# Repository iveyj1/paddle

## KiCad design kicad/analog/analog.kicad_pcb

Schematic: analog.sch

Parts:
C101, C102: 10uF; SMD_1206
C103, C104: 100uF; CP_Radial_D6.3mm_P2.50mm
D101: SS24FL; D_SOD-123
J101: FCI 20021221-00014T4LF; conn_FCI_14_NH
R101: 100k; SMD_0805
U101: NCP694-3.3; SOT89-5

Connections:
+3.3VA: C102.1, C104.1, D101.2, U101.5; also elsewhere on the board
/+3.3V_AN_ENABLE: J101.14, R101.2, U101.3
/+V_UNREG_SW: C101.1, C103.1, D101.1, J101.12, U101.4
/AN0_CS*: J101.5; also elsewhere on the board
/AN1_CS*: J101.3; also elsewhere on the board
/AN2_CS*: J101.1; also elsewhere on the board
/AN3_CS*: J101.2; also elsewhere on the board
/I2C_SCK: J101.6
/I2C_SDA: J101.8
/PIO_A: J101.10
/PIO_B_BUSY*: J101.4; also elsewhere on the board
/SPI_MISO: J101.9; also elsewhere on the board
/SPI_MOSI: J101.7; also elsewhere on the board
/SPI_SCLK: J101.11; also elsewhere on the board
GND: C101.2, C102.2, C103.2, C104.2, J101.13, R101.1, U101.2; also elsewhere on the board

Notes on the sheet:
Note: connector pinout is mirror-image to processor board

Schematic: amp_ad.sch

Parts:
C201, C202, C203: 100pF; SMD_0805
C204, C206, C207: 0.1uF; SMD_0805
C205: 10uF; SMD_1206
Q201: DMG3414U; SOT-23
R201, R205: 10.0k; SMD_0805
R202: 20.0k; SMD_0805
R203, R204: DNP; SMD_0805
U201: LTC2052; TSSOP-8_3x3mm_Pitch0.65mm
U202: ADS1220; TSSOP-16-1EP_4.4x5mm_Pitch0.65mm

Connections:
+3.3VA: C204.2, C205.1, C206.2, C207.2, R205.1, U201.8 (V+), U202.12, U202.13; also elsewhere on the board
/AN0_CS*: U202.2; also elsewhere on the board
/BRIDGE_COMP: R202.2; also elsewhere on the board
/IN_0: R201.2; also elsewhere on the board
/PIO_B_BUSY*: Q201.3; also elsewhere on the board
/SPI_MISO: U202.15; also elsewhere on the board
/SPI_MOSI: U202.16; also elsewhere on the board
/SPI_SCLK: U202.1; also elsewhere on the board
/VREF: U202.11; also elsewhere on the board
GND: C201.1, C202.1, C203.2, C204.1, C205.2, C206.1, C207.1, Q201.2, U201.4 (V-), U202.3, U202.4, U202.5, U202.6, U202.8; also elsewhere on the board
unnamed: C201.2, R201.1, R203.1, U201.3 (+)
unnamed: C202.2, R202.1, R204.1, U201.5 (+)
unnamed: C203.1, R205.2, U202.9
unnamed: Q201.1, U202.14
unnamed: R203.2, U201.1, U201.2 (-), U202.10
unnamed: R204.2, U201.6 (-), U201.7, U202.7

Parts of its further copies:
C501, C502, C503, C601, C602, C603, C701, C702, C703: 100pF; SMD_0805
C504, C506, C507, C604, C606, C607, C704, C706, C707: 0.1uF; SMD_0805
C505, C605, C705: 10uF; SMD_1206
Q501, Q601, Q701: DMG3414U; SOT-23
R501, R505, R601, R605, R701, R705: 10.0k; SMD_0805
R502, R602, R702: 20.0k; SMD_0805
R503, R504, R603, R604, R703, R704: DNP; SMD_0805
U501, U601, U701: LTC2052; TSSOP-8_3x3mm_Pitch0.65mm
U502, U602, U702: ADS1220; TSSOP-16-1EP_4.4x5mm_Pitch0.65mm

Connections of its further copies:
+3.3VA: C504.2, C505.1, C506.2, C507.2, C604.2, C605.1, C606.2, C607.2, C704.2, C705.1, C706.2, C707.2, R505.1, R605.1, R705.1, U501.8 (V+), U502.12, U502.13, U601.8 (V+), U602.12, U602.13, U701.8 (V+), U702.12, U702.13; also elsewhere on the board
/AN1_CS*: U502.2; also elsewhere on the board
/AN2_CS*: U602.2; also elsewhere on the board
/AN3_CS*: U702.2; also elsewhere on the board
/BRIDGE_COMP: R502.2, R602.2, R702.2; also elsewhere on the board
/IN_1: R501.2; also elsewhere on the board
/IN_2: R601.2; also elsewhere on the board
/IN_3: R701.2; also elsewhere on the board
/PIO_B_BUSY*: Q501.3, Q601.3, Q701.3; also elsewhere on the board
/SPI_MISO: U502.15, U602.15, U702.15; also elsewhere on the board
/SPI_MOSI: U502.16, U602.16, U702.16; also elsewhere on the board
/SPI_SCLK: U502.1, U602.1, U702.1; also elsewhere on the board
/VREF: U502.11, U602.11, U702.11; also elsewhere on the board
GND: C501.1, C502.1, C503.2, C504.1, C505.2, C506.1, C507.1, C601.1, C602.1, C603.2, C604.1, C605.2, C606.1, C607.1, C701.1, C702.1, C703.2, C704.1, C705.2, C706.1, C707.1, Q501.2, Q601.2, Q701.2, U501.4 (V-), U502.3, U502.4, U502.5, U502.6, U502.8, U601.4 (V-), U602.3, U602.4, U602.5, U602.6, U602.8, U701.4 (V-), U702.3, U702.4, U702.5, U702.6, U702.8; also elsewhere on the board
unnamed: C501.2, R501.1, R503.1, U501.3 (+)
unnamed: C502.2, R502.1, R504.1, U501.5 (+)
unnamed: C503.1, R505.2, U502.9
unnamed: C601.2, R601.1, R603.1, U601.3 (+)
unnamed: C602.2, R602.1, R604.1, U601.5 (+)
unnamed: C603.1, R605.2, U602.9
unnamed: C701.2, R701.1, R703.1, U701.3 (+)
unnamed: C702.2, R702.1, R704.1, U701.5 (+)
unnamed: C703.1, R705.2, U702.9
unnamed: Q501.1, U502.14
unnamed: Q601.1, U602.14
unnamed: Q701.1, U702.14
unnamed: R503.2, U501.1, U501.2 (-), U502.10
unnamed: R504.2, U501.6 (-), U501.7, U502.7
unnamed: R603.2, U601.1, U601.2 (-), U602.10
unnamed: R604.2, U601.6 (-), U601.7, U602.7
unnamed: R703.2, U701.1, U701.2 (-), U702.10
unnamed: R704.2, U701.6 (-), U701.7, U702.7

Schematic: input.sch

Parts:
J301: CONN_02X05; header-0.050-10-pin-through-hole
R301, R302, R303, R304: 10.0k 0.1%; R_0805
U301: SP3003-04; SMD_SC70-6

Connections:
+3.3VA: J301.1, U301.5; also elsewhere on the board
/IN_0: R301.2, U301.4; also elsewhere on the board
/IN_1: R302.2, U301.6; also elsewhere on the board
/IN_2: R303.2, U301.1; also elsewhere on the board
/IN_3: R304.2, U301.3; also elsewhere on the board
GND: J301.10, U301.2; also elsewhere on the board
unnamed: J301.2, R301.1
unnamed: J301.4, R302.1
unnamed: J301.6, R303.1
unnamed: J301.8, R304.1

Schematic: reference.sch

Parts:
C401, C405: 10uF; SMD_1206
C404, C406: 1uF; SMD_0805
R401: 20k 0.1%; SMD_0805
R402: 20.0k 0.1%; SMD_0805
R404: 1R0; SMD_0805
U401: REF5030; TSSOP-8_3x3mm_Pitch0.65mm

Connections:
+3.3VA: C401.2, R401.2, U401.2; also elsewhere on the board
/BRIDGE_COMP: R401.1, R402.2; also elsewhere on the board
/VREF: C406.1, R404.2, U401.6; also elsewhere on the board
GND: C401.1, C404.2, C405.2, C406.2, R402.1, U401.4; also elsewhere on the board
unnamed: C404.1, U401.5
unnamed: C405.1, R404.1

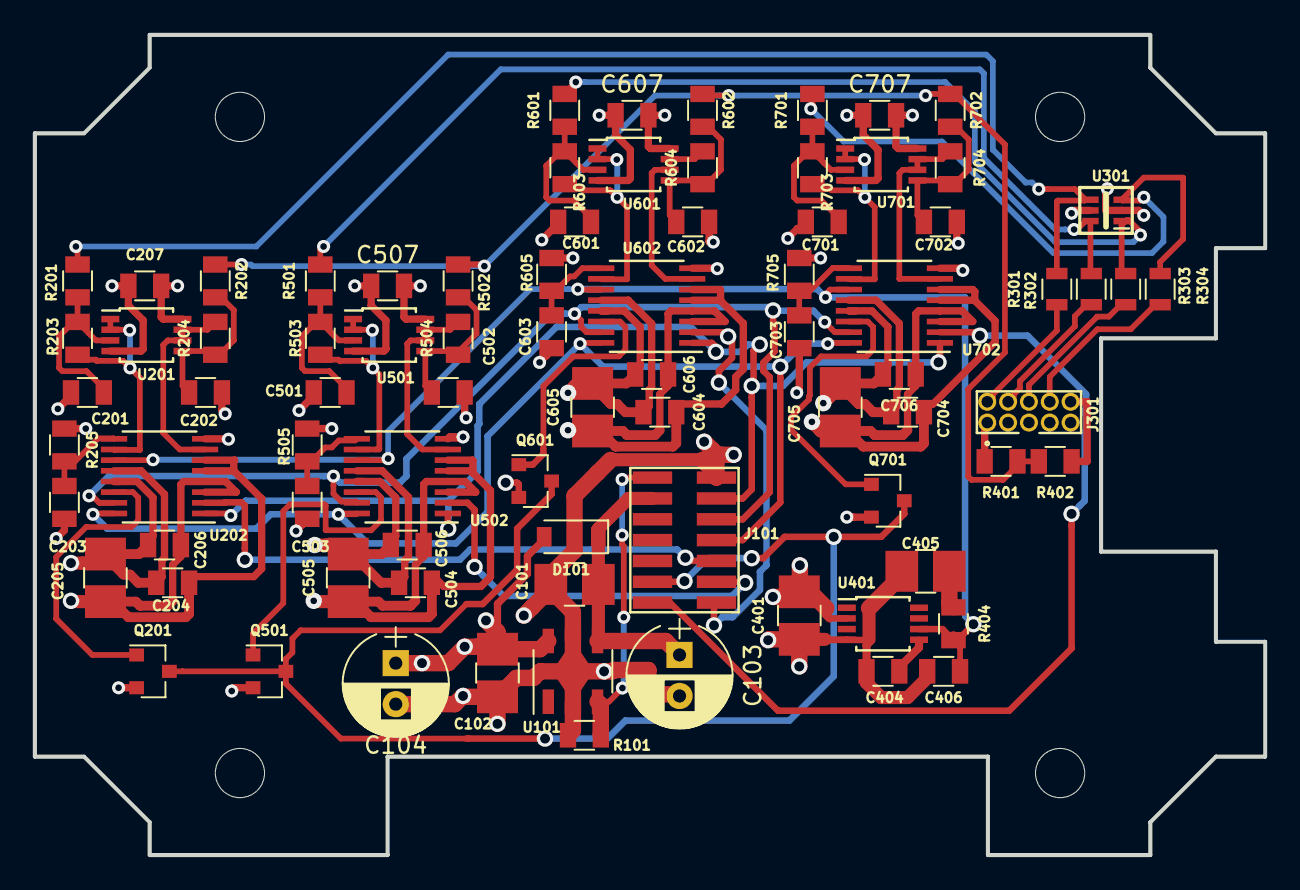
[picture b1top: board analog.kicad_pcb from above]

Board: 4 copper layers, 75.0 x 50.0 mm, 82 parts (0 on the bottom side), 48 nets.

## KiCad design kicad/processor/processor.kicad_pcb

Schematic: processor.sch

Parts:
C101: 1uF; SMD_0805
C102: 10uF; SMD_0805
C103, C104: 0.1uF; SMD_0805
J101: CONN_02X07; conn_FCI_14_NH
LED101, LED102, LED103, LED104, LED105, LED106: LED; SMD_D_0805
R101, R104: 10k; R_0603
R102, R103: 4.7k; R_0603
R105, R106, R108, R109: 330; R_0603
R107, R110: 220; R_0603
U101: ESP32-WROOM
U102: BME280
U103: TCA9534A; SOIC-16

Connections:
+3V3: C102.1, C103.1, C104.1, R101.1, R102.1, R103.1, R104.1, R105.1, U101.2, U102.2, U102.6, U102.8, U103.16; also elsewhere on the board
/1PPS: U101.4; also elsewhere on the board
/+3.3VA_ENABLE: J101.13, U103.9
/+V_UNREG_SW: J101.11; also elsewhere on the board
/AN0_CS*: J101.6, U101.11
/AN1_CS*: J101.4, U101.10
/AN2_CS*: J101.2, U101.9
/AN3_CS*: J101.1, U101.8
/BLINK: R106.1, U101.16
/BOOTLOAD*: U101.25; also elsewhere on the board
/CON_RXD: U101.34; also elsewhere on the board
/CON_TXD: LED101.1, U101.35; also elsewhere on the board
/GPS_ENABLE*: U103.10; also elsewhere on the board
/GPS_RXD: U101.27; also elsewhere on the board
/GPS_TXD: U101.28; also elsewhere on the board
/I2C_SCK: J101.5, R102.2, U101.36, U102.4, U103.14
/I2C_SDA: J101.7, R103.2, U101.33, U102.3, U103.15
/KEEPALIVE: U101.26; also elsewhere on the board
/LEDB: R110.1, U103.7
/LEDG: R107.1, U103.6
/LEDR: R108.1, U103.4
/LEDY: R109.1, U103.5
/PIO_A: J101.9, U103.12
/PIO_B_BUSY*: J101.3, R104.2, U101.7
/POWER_SW*: U101.6; also elsewhere on the board
/RESET_ESP*: C101.1, R101.2, U101.3; also elsewhere on the board
/SD_CS*: U101.29; also elsewhere on the board
/SD_ENABLE*: U103.11; also elsewhere on the board
/SD_MISO: U101.31; also elsewhere on the board
/SD_MOSI: U101.37; also elsewhere on the board
/SD_SCLK: U101.30; also elsewhere on the board
/SPI_MISO: J101.10, U101.13
/SPI_MOSI: J101.8, U101.12
/SPI_SCLK: J101.12, U101.14
GND: C101.2, C102.2, C103.2, C104.2, J101.14, LED102.1, LED103.1, LED104.1, LED105.1, LED106.1, U101.1, U101.15, U101.38, U101.39, U102.1, U102.5, U102.7, U103.1, U103.2, U103.3, U103.8; also elsewhere on the board
unnamed: LED101.2, R105.2
unnamed: LED102.2, R106.2
unnamed: LED103.2, R107.2
unnamed: LED104.2, R108.2
unnamed: LED105.2, R109.2
unnamed: LED106.2, R110.2

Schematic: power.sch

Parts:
C201, C203: 4.7uF; SMD_0805
C202: 10uF; SMD_0805
C204, C205: 100uF/10V; CP_Radial_D6.3mm_P2.50mm
D201, D202, D203, D204: SS24FL; D_SOD-123
F201: 1A Poly; SMD_1812
J201, J203: S2B-PH-K-S(LF)(SN); JST_battery_header_B2B-PH-K-S
LED201: LED; SMD_D_0805
Q201, Q202, Q204, Q205: DMG3415U; SOT-23
Q203: DMG3414U; SOT-23
R201, R202, R210: 1.0Meg; R_0603
R203: 1.0K; R_0603
R204, R205: 100k; R_0603
R206: 1.0k; R_0603
R207, R208: 1Meg; R_0603
R209: 10K; R_0603
R211: 1R0; R_0603
SW201: SW; SW_KMR7
U201: MCP73832; SOT-23-5
U202: NCP694-3.3; SOT89-5

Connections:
+3V3: C205.1, D204.2, U202.5; also elsewhere on the board
/+V_UNREG_SW: C204.1, D204.1, Q204.3, U202.3, U202.4; also elsewhere on the board
/KEEPALIVE: D203.2; also elsewhere on the board
/POWER_SW*: R204.1; also elsewhere on the board
/USB/+VBUS: Q201.1, Q202.3, R202.1; also elsewhere on the board
/power/V+BAT: F201.2, J203.1
/power/V+BAT_FUSED: C203.1, F201.1, Q205.3, U201.3 (Vbat)
/power/V+EXT: C201.1, D201.2, Q201.2, Q202.2, Q205.1, R203.1, R210.2, U201.4 (VDD)
/power/V_UNREG: Q204.2, R208.2, R211.1, SW201.2
GND: C201.2, C202.2, C203.2, C204.2, C205.2, J201.2, J203.2, Q203.2, R201.2, R202.2, R205.1, R207.1, R209.1, R210.1, U201.2 (Vss), U202.2; also elsewhere on the board
unnamed: C202.1, D203.1, Q203.1, R206.1, R207.2
unnamed: D201.1, Q205.2, R211.2
unnamed: D202.1, R206.2
unnamed: D202.2, R204.2, R205.2, SW201.1
unnamed: J201.1, Q201.3, Q202.1, R201.1
unnamed: LED201.1, U201.1 (STAT)
unnamed: LED201.2, R203.2
unnamed: Q203.3, Q204.1, R208.1
unnamed: R209.2, U201.5 (PROG)

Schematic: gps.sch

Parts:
BT301: CR1025; CR1025_holder
C301: 10uF; SMD_0805
C302: 0.01uF; SMD_0805
C303: 1uF; SMD_0805
L301: bead; SMD_0805
LED301: LED; SMD_D_0805
Q301: DMG3415U; SOT-23
R301: 1MEG; R_0603
R302, R303, R304: 330; R_0603
U301: FGPMMOPA6H

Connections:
+3V3: Q301.2, R301.1; also elsewhere on the board
/1PPS: U301.13; also elsewhere on the board
/GPS_ENABLE*: Q301.1, R301.2; also elsewhere on the board
/GPS_RXD: R302.1; also elsewhere on the board
/GPS_TXD: R303.1; also elsewhere on the board
GND: BT301.-, C301.2, C302.2, C303.2, LED301.1, U301.3, U301.8, U301.12, U301.19; also elsewhere on the board
unnamed: BT301.+, C303.1, U301.4
unnamed: C301.1, C302.1, L301.1, U301.1
unnamed: L301.2, Q301.3
unnamed: LED301.2, R304.1
unnamed: R302.2, U301.9
unnamed: R303.2, U301.10
unnamed: R304.2, U301.5

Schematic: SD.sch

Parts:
C501: 10uF; SMD_1206
C502: 0.1uF; SMD_0805
M501: MICROSD
Q501: DMG3415U; SOT-23
R501: 1MEG; SMD_0805

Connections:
+3V3: R501.2; also elsewhere on the board
/BOOTLOAD*: Q501.3; also elsewhere on the board
GND: C501.2, C502.2; also elsewhere on the board
unnamed 44: C501.1, C502.1; also elsewhere on the board
unnamed 66: Q501.1; also elsewhere on the board
unnamed 67: Q501.2; also elsewhere on the board
unnamed 74: R501.1; also elsewhere on the board

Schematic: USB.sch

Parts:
C501: 10uF; SMD_0805
C502: 0.1uF; SMD_0805
LED501, LED502: LED; SMD_D_0805
Q501, Q502: MMBT4401; SOT-23
R501: 1k; R_0603
R502, R503: 330; R_0603
R504, R505: 10k; R_0603
SW501, SW502: SWITCH_PUSHBUTTON; SW_KMR7
TP501: RXD; tp_th_1mm
TP502: TXD; tp_th_1mm
U501: USB_B_Socket; USB_micro_B_FCI_10104110
U502: SP3003-04; SMD_SC70-6
U503: CP2102N; QFP_24

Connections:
+3V3: R501.2; also elsewhere on the board
/BOOTLOAD*: Q501.3, SW502.1; also elsewhere on the board
/CON_RXD: TP502.1, U503.21; also elsewhere on the board
/CON_TXD: TP501.1, U503.20; also elsewhere on the board
/RESET_ESP*: Q502.3, SW501.1; also elsewhere on the board
/USB/+VBUS: U501.1, U502.1, U503.7, U503.8; also elsewhere on the board
GND: C501.2, C502.2, SW501.2, SW502.2, U501.5, U501.6, U502.2, U503.2, U503.25; also elsewhere on the board
unnamed: C501.1, C502.1, LED501.2, LED502.2, U503.6
unnamed: LED501.1, R502.2
unnamed: LED502.1, R503.2
unnamed: Q501.1, R505.2
unnamed: Q501.2, R504.2, U503.23
unnamed: Q502.1, R504.1
unnamed: Q502.2, R505.1, U503.19
unnamed: R501.1, U503.9
unnamed: R502.1, U503.14
unnamed: R503.1, U503.13
unnamed 77: U503.5; also elsewhere on the board
unnamed: U501.2, U502.3, U503.4
unnamed: U501.3, U502.4, U503.3

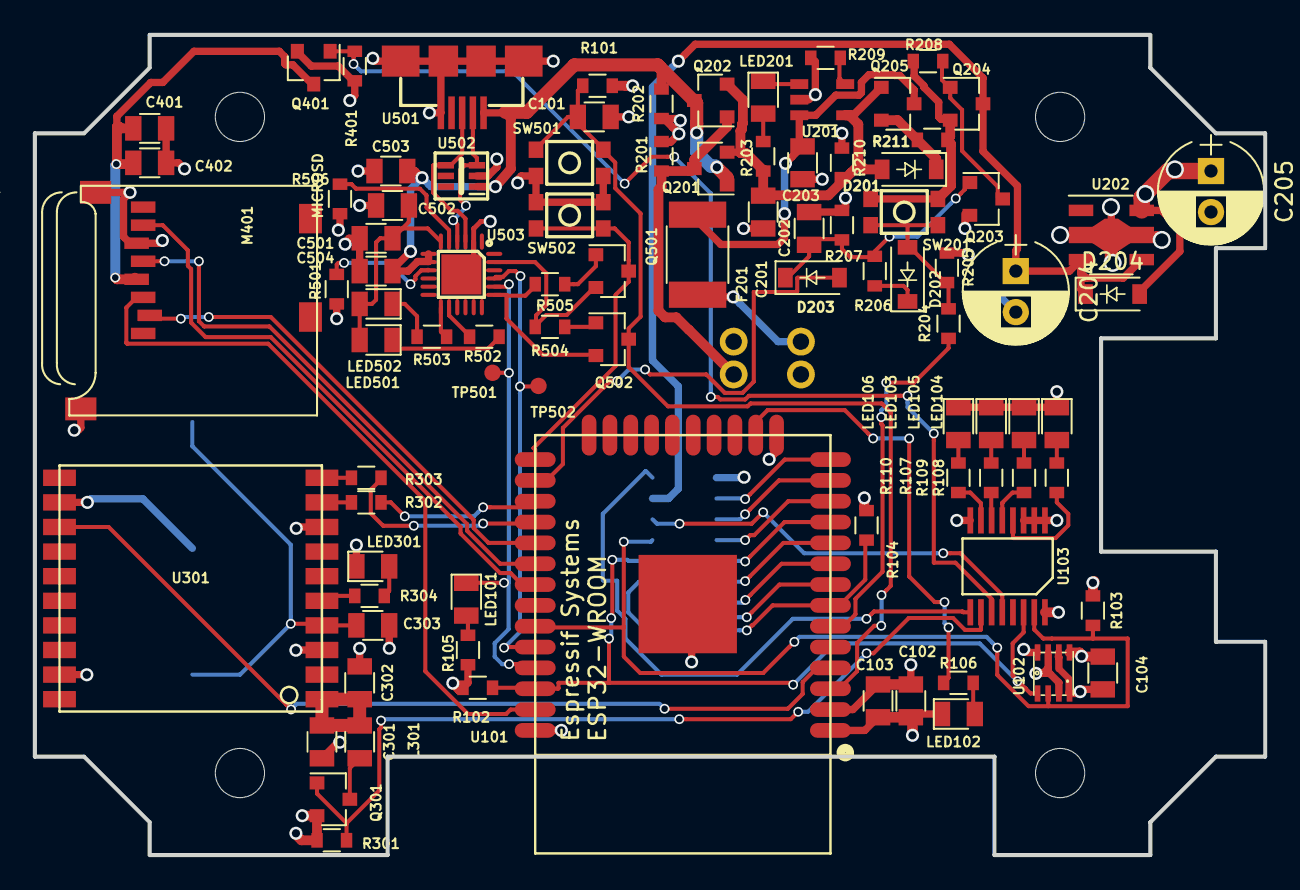
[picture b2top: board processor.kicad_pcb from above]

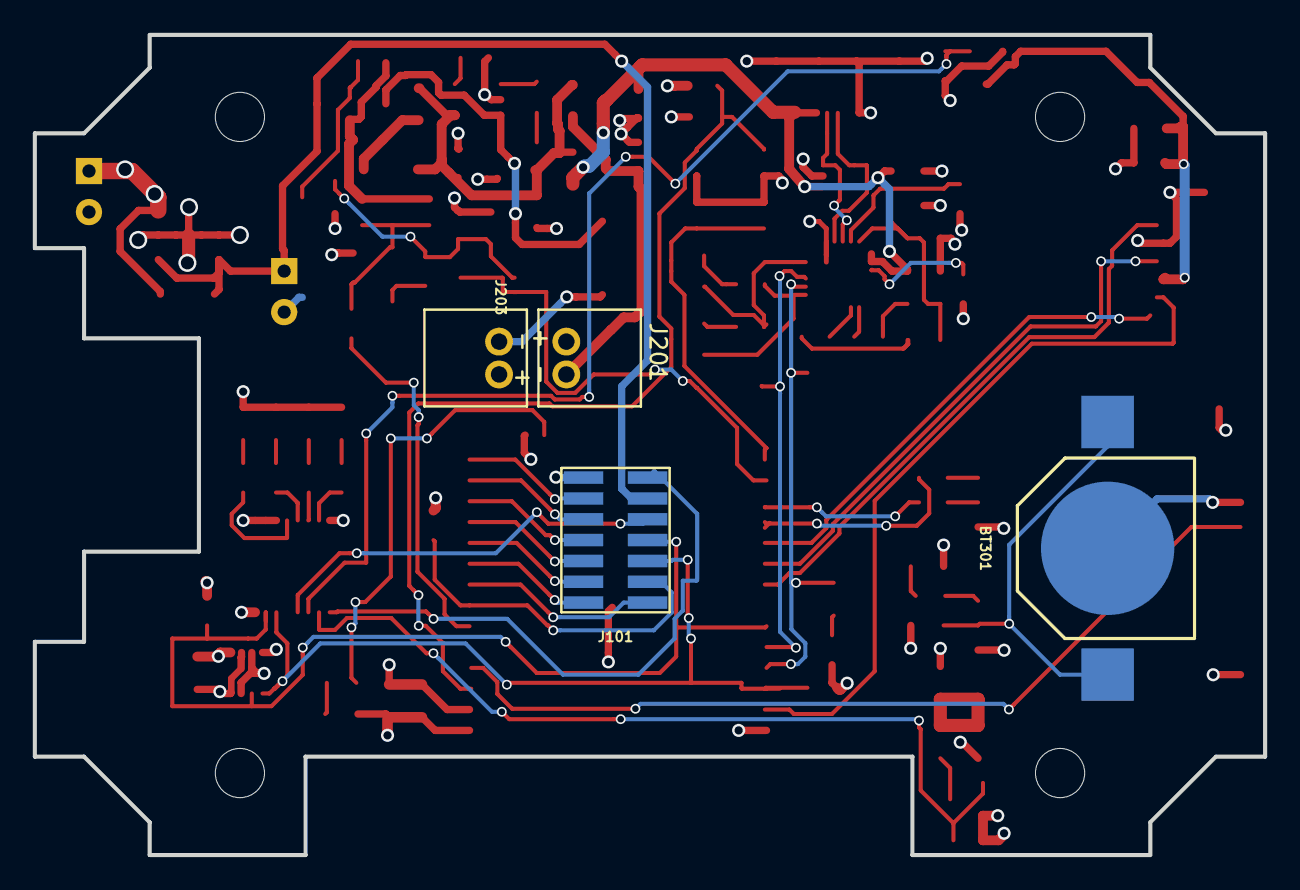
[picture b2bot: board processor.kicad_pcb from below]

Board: 4 copper layers, 75.0 x 50.0 mm, 94 parts (4 on the bottom side), 76 nets.

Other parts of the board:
C401: 10uF; SMD_0805
C402, C504: 0.1uF; SMD_0805
C503: 4.7uF; SMD_0805
M401: MICROSD
Q401: DMG3415U; SOT-23
R401: 1MEG; R_0603
R506: 1k; R_0603

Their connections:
+3V3: Q401.2, R401.1, R506.1; also elsewhere on the board
/SD_CS*: M401.2; also elsewhere on the board
/SD_ENABLE*: Q401.1, R401.2; also elsewhere on the board
/SD_MISO: M401.7; also elsewhere on the board
/SD_MOSI: M401.3; also elsewhere on the board
/SD_SCLK: M401.5; also elsewhere on the board
/USB/+VBUS: C503.1, C504.1; also elsewhere on the board
GND: C401.2, C402.2, C503.2, C504.2, M401.6, M401.MT1, M401.MT2; also elsewhere on the board
unnamed: C401.1, C402.1, M401.4, Q401.3
unnamed 77: R506.2; also elsewhere on the board

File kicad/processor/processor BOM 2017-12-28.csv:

Id,Designator,Package,Quantity,Designation,Supplier and ref
8,U101,ESP32-WROOM,1,ESP32-WROOM,1 stock
25,U301,FGPMMOPA6H,1,FGPMMOPA6H,1 stock
18,F201,SMD_1812,1,1A Poly,10 stock
24,SW201,SW_KMR7,1,SW,10 stock
12,"SW501,SW502",SW_KMR7,2,SWITCH_PUSHBUTTON,10 stock
29,"C303,C101",SMD_0805,2,1uF,100 stock
3,"C401,C301,C202,C102,C205,C204,C501",SMD_0805,7,10uF,100 stock
23,U202,SOT89-5,1,NCP694-3.3,17 stock
41,Q203,SOT-23,1,DMG3414U,20 stock
11,"Q301,Q401,Q205,Q204,Q202,Q201",SOT-23,6,DMG3415U,20 stock
28,"C402,C104,C103,C502",SMD_0805,4,0.1uF,200 stock
15,U501,USB_micro_B_FCI_10104110,1,USB_B_Socket,5 stock
22,U201,SOT-23-5,1,MCP73832,ncp73831 ok
26,"C203,C201",SMD_0805,2,4.7uF,stock
31,"LED102,LED103,LED104,LED105,LED106,LED101,LED201,LED301,LED502,LED501",SMD_D_0805,10,LED,Stock
19,J201,TH_1.0,1,V_QI,x
20,J202,TH_1.0,1,GND,x
4,",REF**,REF**,",KH_F20_mounting_hole,4,hole,x
17,BT301,CR1025_holder,1,CR1025,5 DK
30,C302,SMD_0805,1,0.01uF,100 stock
16,"D201,D204,D203,D202",D_SOD-123,4,SS24FL,25 DK
43,J101,conn_FCI_14_NH,1,CONN_02X07,4 DK
21,J203,JST_battery_header_S2B-PH-K-S,1,Battery,4 DK
27,L301,SMD_0805,1,bead,10 DK
1,M401,MICROSD,1,MICROSD,5DK 2908-05WB
42,"Q502,Q501",SOT-23,2,MMBT4401,100 DK
36,"R103,R102",R_0603,2,4.7k,100 DK
9,"R104,R101,R505,R504",R_0603,4,10k,100 DK
35,"R202,R201,R210",R_0603,3,1.0Meg,100 DK
34,R203,R_0603,1,1.0K,100 DK
39,R204,R_0603,1,100k,100 DK
32,"R205,R208,R207",R_0603,3,1Meg,100 DK
38,R206,R_0603,1,1.0k,100 DK
37,R209,R_0603,1,10K,100 DK
10,"R301,R401",R_0603,2,1MEG,100 DK
33,"R304,R303,R302,R110,R109,R108,R107,R106,R105,R502,R503",R_0603,11,330,100 DK
40,R501,R_0603,1,1k,100 DK
13,TP501,tp_th_1mm,1,RXD,x
7,TP502,tp_th_1mm,1,TXD,x
6,U102,BME280,1,BME280,3 DK
5,U103,SOIC-16,1,TCA9534A,5 DK
14,U502,SMD_SC70-6,1,SP3003-04,10DK
2,U503,QFP_24,1,CP2102N,5 DK

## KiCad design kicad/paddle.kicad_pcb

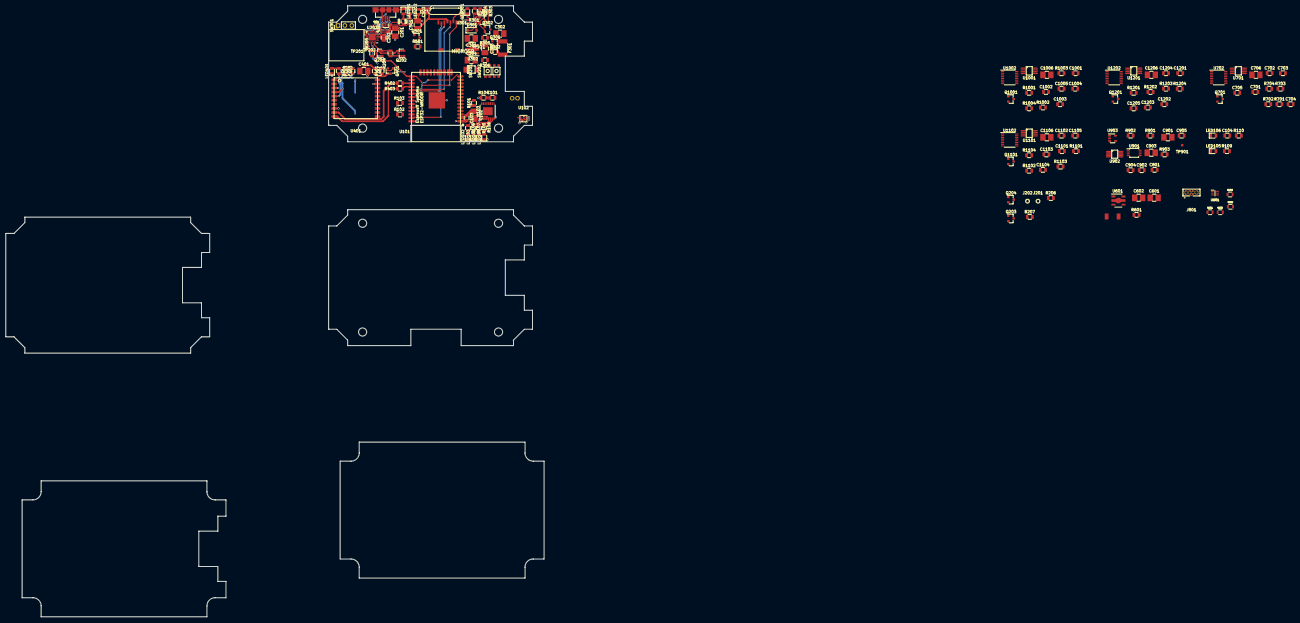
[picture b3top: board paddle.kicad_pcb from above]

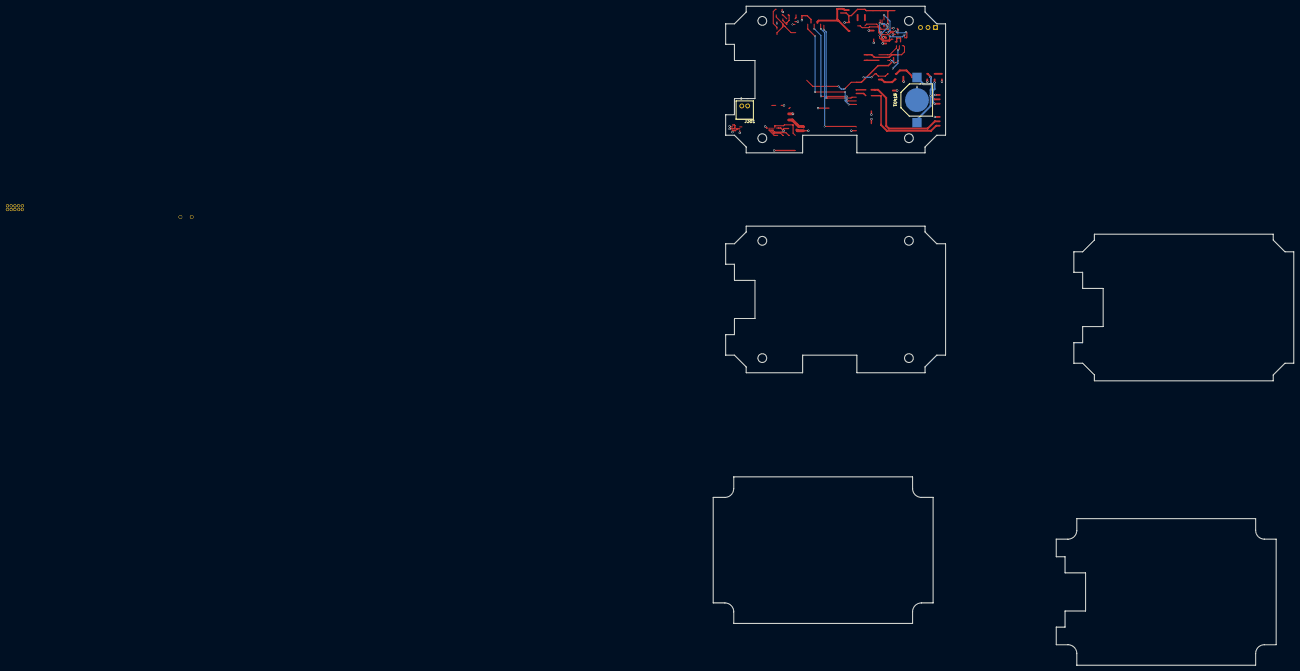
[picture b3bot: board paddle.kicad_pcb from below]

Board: 4 copper layers, 161 parts (2 on the bottom side), 97 nets.

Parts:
BT401: CR1025; CR1025_holder
C101, C403, C704, C902, C904, C1004, C1104, C1204: 1uF; SMD_0805
C102, C201, C303, C304, C401, C501, C601, C602, C706, C901, C903, C1006, C1106, C1206: 10uF; SMD_1206
C103, C104, C202, C502, C702, C705, C905, C1002, C1005, C1102, C1105, C1202, C1205: 0.1uF; SMD_0805
C301, C302: 4.7uF; SMD_1206
C402, C701, C703, C801, C1001, C1003, C1101, C1103, C1201, C1203: 0.01uF; SMD_0805
D301: RB168LAM-30; D_SOD-123
D302: RB168LAM-30; D_SOD-128
D601: RB168LAM; D_SOD-128
F301: 1A Poly; SMD_1812
J201: V_QI; TH_1.0
J202: GND; TH_1.0
J301: Battery; JST_battery_header_B2B-PH-K-S
J801: CONN_02X05; header-0.050-10-pin-through-hole
L401: bead; SMD_0805
LED101, LED102, LED103, LED104, LED105, LED106, LED201, LED202, LED401: LED; SMD_D_0805
LED301: Charge; SMD_D_0805
M501: MICROSD
Q201, Q202: MMBT4401; SOT-23
Q203, Q204, Q302, Q303, Q401, Q501: DMG3415U; SOT-23
Q301, Q701, Q1001, Q1101, Q1201: DMG3414U; SOT-23
R101, R102, R204, R205, R306, R701, R1001, R1101, R1201: 10k; SMD_0805
R103, R104: 4.7k; SMD_0805
R105, R106, R107, R108, R109, R110, R402, R403, R404: 330; SMD_0805
R201: 1k; R_0805
R202, R203: 330; R_0805
R206, R207, R305: 1.0Meg; SMD_0805
R301: 1.0K; SMD_0805
R302, R303: 1Meg; SMD_0805
R304: 10K; SMD_0805
R401, R501: 1MEG; SMD_0805
R601: 100k; SMD_0805
R702, R1002, R1102, R1202: DNP; SMD_0805
R703, R1003, R1103, R1203: 10; SMD_0805
R704, R1004, R1104, R1204: 5k; SMD_0805
R801, R802, R803, R804: 10k 0.1%; R_0805
R901, R902: 20k 0.1%; SMD_0805
R903: 1R0; SMD_0805
SW201, SW202: SWITCH_PUSHBUTTON; SW_KMR7
SW301: SW_SPDT; Pin_Header_Straight_1x03_Pitch2.54mm
TP201: RXD; tp_th_1mm
TP202: TXD; tp_th_1mm
TP901: VREF; tp_th_1mm
U101: ESP32-WROOM
U102: BME280
U103: TCA9534A; TSSOP-16-1EP_4.4x5mm_Pitch0.65mm
U201: USB_B_Socket; USB_micro_B_FCI_10104110
U202, U801: SP3003-04; SMD_SC70-6
U203: CP2102N; QFN-24-1EP_4x4mm_Pitch0.5mm
U301: MCP73832; SOT-23-5
U302, U601: NCP694-3.3; SOT89-5
U401: FGPMMOPA6H GPS; FGPMMOPA6H
U701, U1001, U1101, U1201: OPA388D; S-PDSO-G8
U702, U1002, U1102, U1202: LTC2440; SSOP-16_3.9x4.9mm_Pitch0.635mm
U901: REF5030; TSSOP-8_3x3mm_Pitch0.65mm
U902: TS5A3160; VSSOP10-S-PDSO-G10
U903: OPA333; sot23-5

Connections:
+3.3VA: C602.1, C702.2, C705.2, C706.1, C901.1, C905.1, C1002.2, C1005.2, C1006.1, C1102.2, C1105.2, C1106.1, C1202.2, C1205.2, C1206.1, D601.1, J801.1, R901.2, U601.5, U701.7, U702.2, U901.2, U902.5, U903.5, U1001.7, U1002.2, U1101.7, U1102.2, U1201.7, U1202.2
+3V3: C102.1, C103.1, C104.1, C201.1, C202.1, C304.1, D302.1, Q401.2, Q501.2, R101.1, R102.1, R103.1, R104.1, R201.2, R501.1, U101.2, U102.2, U102.6, U102.8, U202.5, U203.5, U203.6, U203.7, U302.5, U801.5
/1PPS: U101.4, U401.13
/+V_UNREG_SW: C303.1, C601.1, D302.2, D601.2, Q302.3, SW301.2, U302.3, U302.4, U601.4
/BLINK: R110.1, U101.11
/BOOTLOAD*: Q201.3, SW202.1, U101.25
/BUSY*: Q701.3, Q1001.3, Q1101.3, Q1201.3, R101.2, U101.5
/CS_SD*: M501.2, U101.29
/ENABLE_+3.3VA: R601.2, U103.9, U601.3
/ENABLE_GPS*: Q401.1, R401.2, U103.10
/KEEPALIVE: Q301.1, R302.2, U101.26
/LEDB: R108.1, U103.7
/LEDG: R105.1, U103.6
/LEDR: R106.1, U103.4
/LEDY: R107.1, U103.5
/Power/+VBUS: Q203.1, Q204.3, R207.1, U201.1, U202.6, U203.8
/Power/+V_CHARGE: C301.1, D301.1, Q203.2, Q204.2, Q303.1, R301.1, R305.2, U301.4
/Power/V_BAT: C302.1, F301.1, Q303.3, U301.3
/Power/V_UNREG: D301.2, Q302.2, Q303.2, R303.2, SW301.1
/RESET_ESP*: C101.1, Q202.3, R102.2, SW201.1, U101.3
/RXD_CON: TP202.1, U101.34, U203.21
/RXD_GPS: R402.1, U101.27
/SCK_I2C: R103.2, U101.36, U102.4, U103.14
/SCLK_SPI: M501.5, U101.30, U702.13, U1002.13, U1102.13, U1202.13
/SDA_I2C: R104.2, U101.33, U102.3, U103.15
/SDI_SPI: M501.7, U101.31
/SDO_SPI: M501.3, U101.37, U702.7, U702.12, U1002.7, U1002.12, U1102.7, U1102.12, U1202.7, U1202.12
/SD_ENABLE*: Q501.1, R501.2
/SHUTDOWN*: R306.2, SW301.3, U101.7
/TXD_CON: TP201.1, U101.35, U203.20
/TXD_GPS: R403.1, U101.28
/analog/IN_0: R701.2, R801.2, U801.6
/analog/IN_1: R802.2, R1001.2, U801.4
/analog/IN_2: R803.2, R1101.2, U801.3
/analog/IN_3: R804.2, R1201.2, U801.1
/analog/VREF: R702.2, R1002.2, R1102.2, R1202.2, TP901.1, U702.3, U702.6, U903.1, U903.4, U1002.3, U1002.6, U1102.3, U1102.6, U1202.3, U1202.6
GND: BT401.-, C101.2, C102.2, C103.2, C104.2, C201.2, C202.2, C301.2, C302.2, C303.2, C304.2, C401.2, C402.2, C403.2, C501.2, C502.2, C601.2, C602.2, C701.1, C702.1, C704.2, C705.1, C706.2, C801.2, C901.2, C902.2, C903.2, C904.2, C905.2, C1001.1, C1002.1, C1004.2, C1005.1, C1006.2, C1101.1, C1102.1, C1104.2, C1105.1, C1106.2, C1201.1, C1202.1, C1204.2, C1205.1, C1206.2, J202.1, J301.2, J801.10, LED101.K, LED102.K, LED103.K, LED104.K, LED105.K, LED106.K, LED201.K, LED202.K, LED401.K, M501.6, M501.MT1, M501.MT2, Q301.2, Q701.2, Q1001.2, Q1101.2, Q1201.2, R206.2, R207.2, R302.1, R304.1, R305.1, R306.1, R601.1, R902.1, SW201.2, SW202.2, U101.1, U101.15, U101.38, U101.39, U102.1, U102.5, U102.7, U103.1, U103.2, U103.3, U103.8, U201.5, U201.6, U202.2, U203.2, U203.25, U301.2, U302.2, U401.3, U401.8, U401.12, U401.19, U601.2, U701.4, U702.1, U702.4, U702.8, U702.9, U702.10, U702.14, U702.16, U801.2, U901.4, U902.2, U903.2, U1001.4, U1002.1, U1002.4, U1002.8, U1002.9, U1002.10, U1002.14, U1002.16, U1101.4, U1102.1, U1102.4, U1102.8, U1102.9, U1102.10, U1102.14, U1102.16, U1201.4, U1202.1, U1202.4, U1202.8, U1202.9, U1202.10, U1202.14, U1202.16
unnamed: BT401.+, C403.1, U401.4
unnamed: C401.1, C402.1, L401.1, U401.1
unnamed: C501.1, C502.1, M501.4, Q501.3
unnamed: C701.2, R701.1, U701.3
unnamed: C703.1, R703.1, U701.6
unnamed: C703.2, R702.1, R704.1, U701.2
unnamed: C704.1, R703.2, R704.2, U702.5
unnamed: C801.1, R901.1, R902.2, U902.3
unnamed: C902.1, U901.5
unnamed: C903.1, R903.1
unnamed: C904.1, R903.2, U901.6, U902.1
unnamed: C1001.2, R1001.1, U1001.3
unnamed: C1003.1, R1003.1, U1001.6
unnamed: C1003.2, R1002.1, R1004.1, U1001.2
unnamed: C1004.1, R1003.2, R1004.2, U1002.5
unnamed: C1101.2, R1101.1, U1101.3
unnamed: C1103.1, R1103.1, U1101.6
unnamed: C1103.2, R1102.1, R1104.1, U1101.2
unnamed: C1104.1, R1103.2, R1104.2, U1102.5
unnamed: C1201.2, R1201.1, U1201.3
unnamed: C1203.1, R1203.1, U1201.6
unnamed: C1203.2, R1202.1, R1204.1, U1201.2
unnamed: C1204.1, R1203.2, R1204.2, U1202.5
unnamed: F301.2, J301.1
unnamed: J201.1, Q203.3, Q204.1, R206.1
unnamed: J801.2, R801.1
unnamed: J801.4, R802.1
unnamed: J801.6, R803.1
unnamed: J801.8, R804.1
unnamed: L401.2, Q401.3
unnamed: LED101.A, R105.2
unnamed: LED102.A, R106.2
unnamed: LED103.A, R107.2
unnamed: LED104.A, R108.2
unnamed: LED105.A, R109.2
unnamed: LED106.A, R110.2
unnamed: LED201.A, R202.2
unnamed: LED202.A, R203.2
unnamed: LED301.A, R301.2
unnamed: LED301.K, U301.1
unnamed: LED401.A, R404.1
unnamed: Q201.1, R205.1
unnamed: Q201.2, R204.2, U203.23
unnamed: Q202.1, R204.1
unnamed: Q202.2, R205.2, U203.19
unnamed: Q301.3, Q302.1, R303.1
unnamed: Q701.1, U702.15
unnamed: Q1001.1, U1002.15
unnamed: Q1101.1, U1102.15
unnamed: Q1201.1, U1202.15
unnamed: R201.1, U203.9
unnamed: R202.1, U203.14
unnamed: R203.1, U203.13
unnamed: R304.2, U301.5
unnamed: R402.2, U401.9
unnamed: R403.2, U401.10
unnamed: R404.2, U401.5
unnamed: U201.2, U202.3, U203.4
unnamed: U201.3, U202.4, U203.3
unnamed: U902.4, U903.3
